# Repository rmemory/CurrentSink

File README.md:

Building a current sink for battery testing

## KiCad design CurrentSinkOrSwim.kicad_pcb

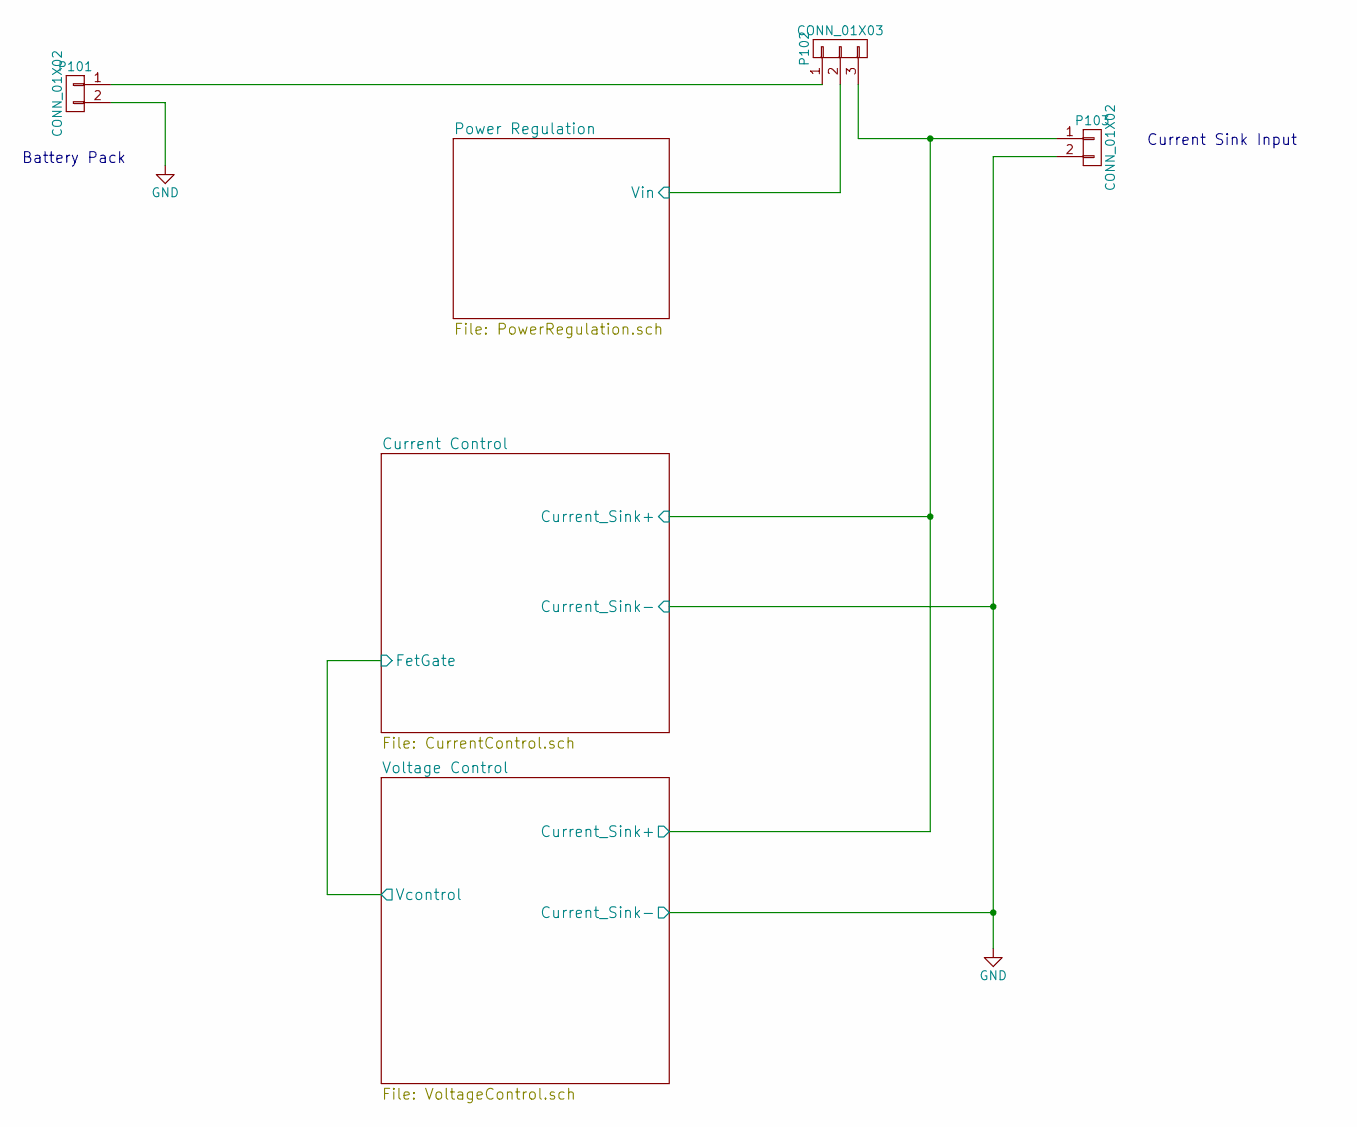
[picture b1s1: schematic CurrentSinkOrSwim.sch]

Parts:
P101, P103: CONN_01X02; Terminal_Block_200_mil; MPN OSTTC022162
P102: CONN_01X03; Pin_Header_Straight_1x03

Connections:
/Current Control/Current_Sink+: P102.3, P103.1; also elsewhere on the board
/Power Regulation/Vin: P102.2; also elsewhere on the board
GND: P101.2, P103.2; also elsewhere on the board
unnamed: P101.1, P102.1

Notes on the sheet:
Battery Pack
Current Sink Input

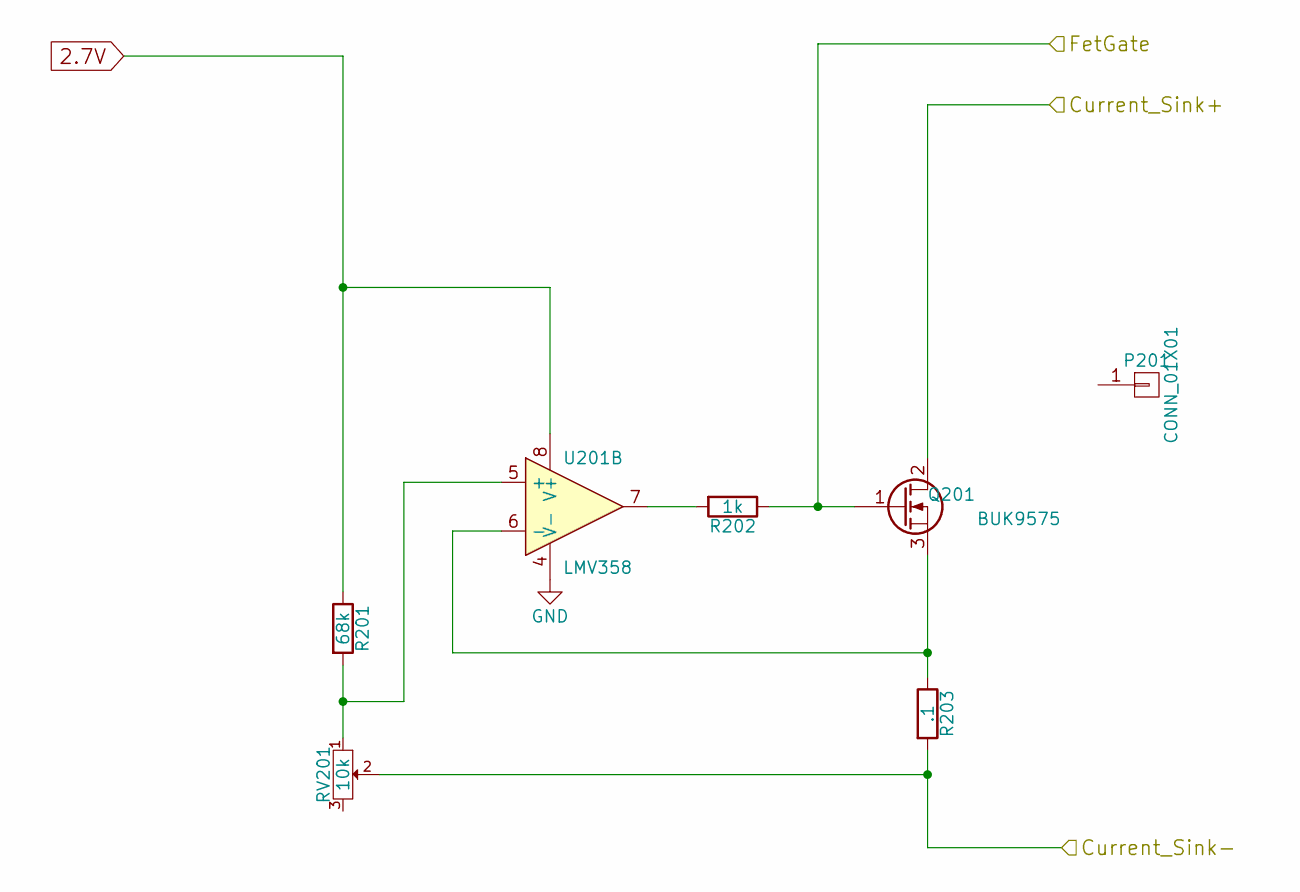
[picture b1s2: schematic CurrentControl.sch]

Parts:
P201: CONN_01X01; FA-T220-38E-ND; MPN FA-T220-38E-ND
Q201: BUK9575; TO-220_Neutral123_Vertical; MPN BUK9575-100A,127
R201: 68k; R_0805
R202: 1k; R_0805
R203: .1; Resistor_Horizontal_RM15mm; MPN AC01000001007JA100
RV201: 10k; P090L-02F25BR10K; MPN P090L-02F25BR10K
U201: LMV358; SOIC-8-N; MPN LMV358IDT

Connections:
2.7V: R201.1, U201.8 (V+); also elsewhere on the board
/Current Control/Current_Sink+: Q201.2 (D); also elsewhere on the board
/Current Control/FetGate: Q201.1 (G), R202.1; also elsewhere on the board
GND: R203.2, RV201.2, U201.4 (V-); also elsewhere on the board
unnamed: Q201.3 (S), R203.1, U201.6 (-)
unnamed: R201.2, RV201.1, U201.5 (+)
unnamed: R202.2, U201.7

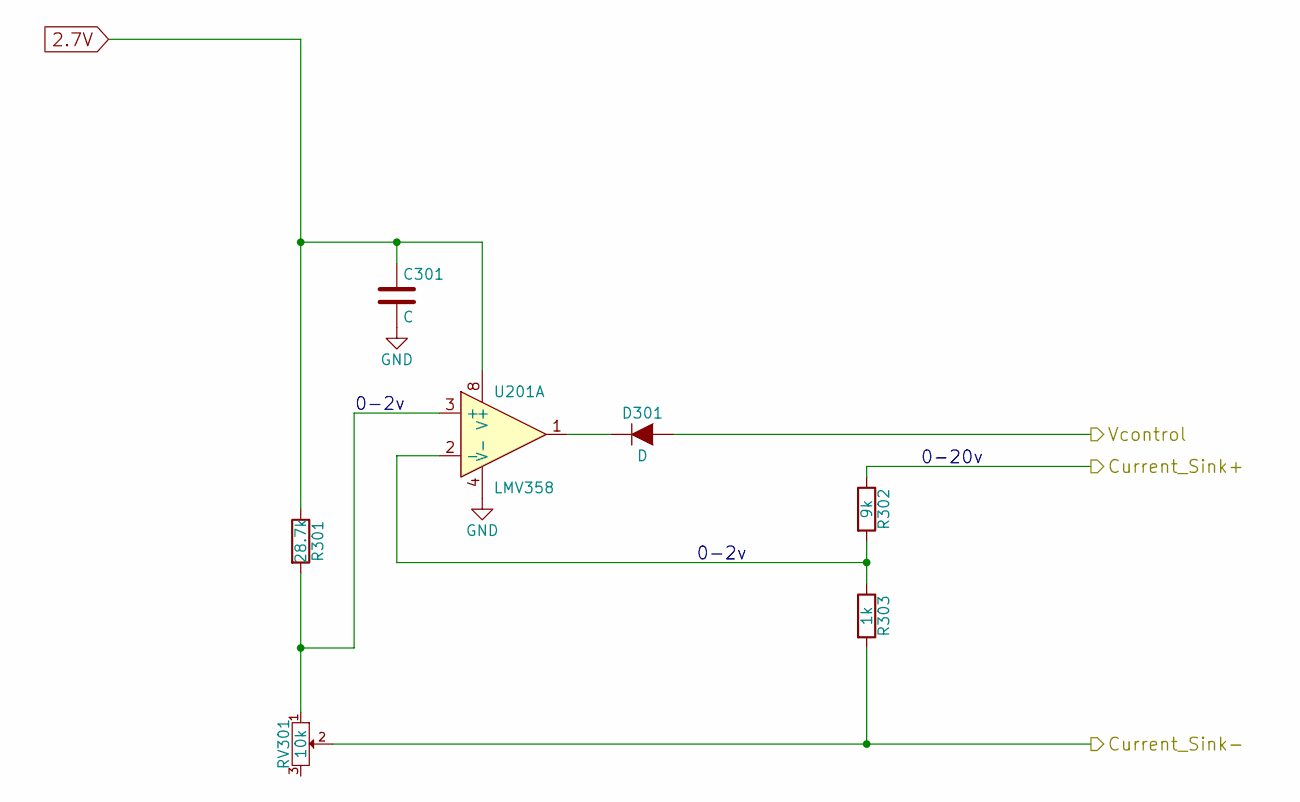
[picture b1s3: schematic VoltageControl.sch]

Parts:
C301: C; C_0805
D301: D; SMB-SMC_Universal_Handsoldering; MPN CD214B-R3600
R301: 28.7k; R_0805
R302: 9k; R_0805
R303: 1k; R_0805
RV301: 10k; P090L-02F25BR10K
U201: LMV358; SOIC-8-N; MPN LMV358IDT

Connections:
2.7V: C301.1, R301.1, U201.8 (V+); also elsewhere on the board
/Current Control/Current_Sink+: R302.1; also elsewhere on the board
/Current Control/FetGate: D301.2 (A); also elsewhere on the board
GND: C301.2, R303.2, RV301.2, U201.4 (V-); also elsewhere on the board
unnamed: D301.1 (K), U201.1
unnamed: R301.2, RV301.1, U201.3 (+)
unnamed: R302.2, R303.1, U201.2 (-)

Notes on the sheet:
0-2v
0-20v

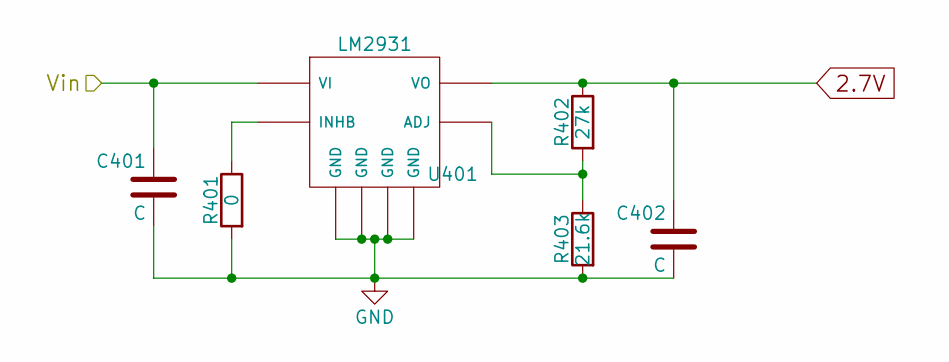
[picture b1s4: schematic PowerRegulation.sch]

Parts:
C401, C402: C; C_0805
R401: 0; R_0805
R402: 27k; R_0805
R403: 21.6k; R_0805
U401: LM2931; SOIC-8-N; MPN LM2931D-R

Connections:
2.7V: C402.1, R402.1, U401.1 (VO); also elsewhere on the board
/Power Regulation/Vin: C401.1, U401.8 (VI); also elsewhere on the board
GND: C401.2, C402.2, R401.2, R403.2, U401.2 (GND), U401.3 (GND), U401.6 (GND), U401.7 (GND); also elsewhere on the board
unnamed: R401.1, U401.5 (INHB)
unnamed: R402.2, R403.1, U401.4 (ADJ)

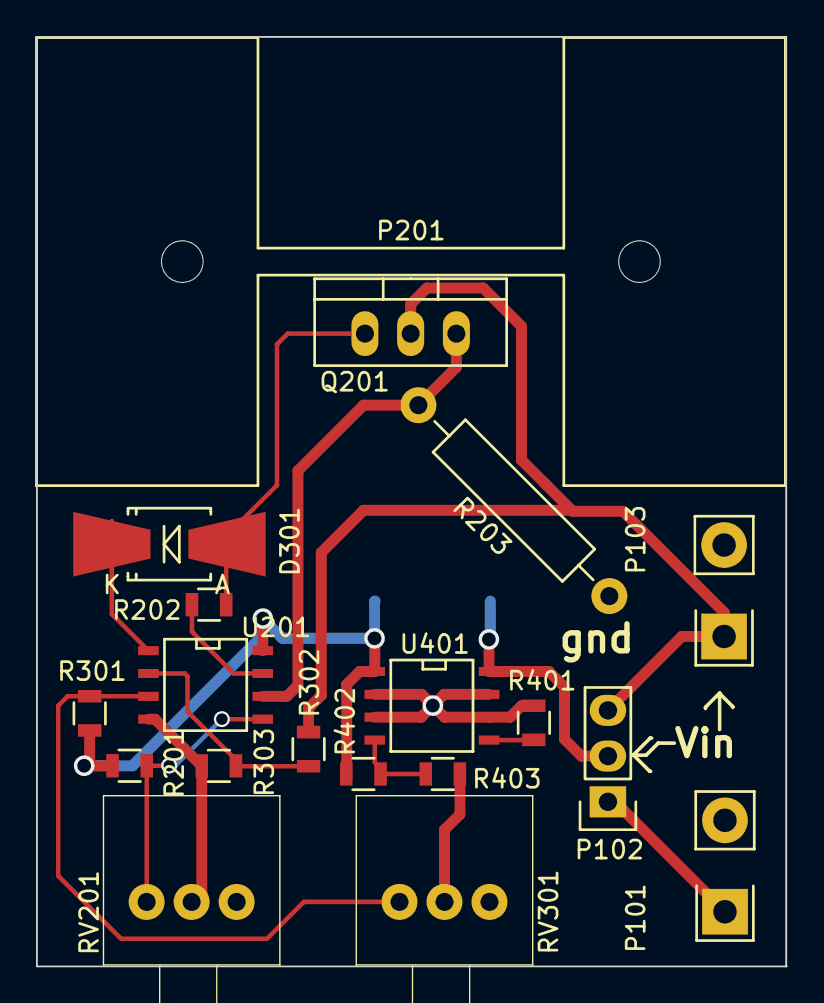
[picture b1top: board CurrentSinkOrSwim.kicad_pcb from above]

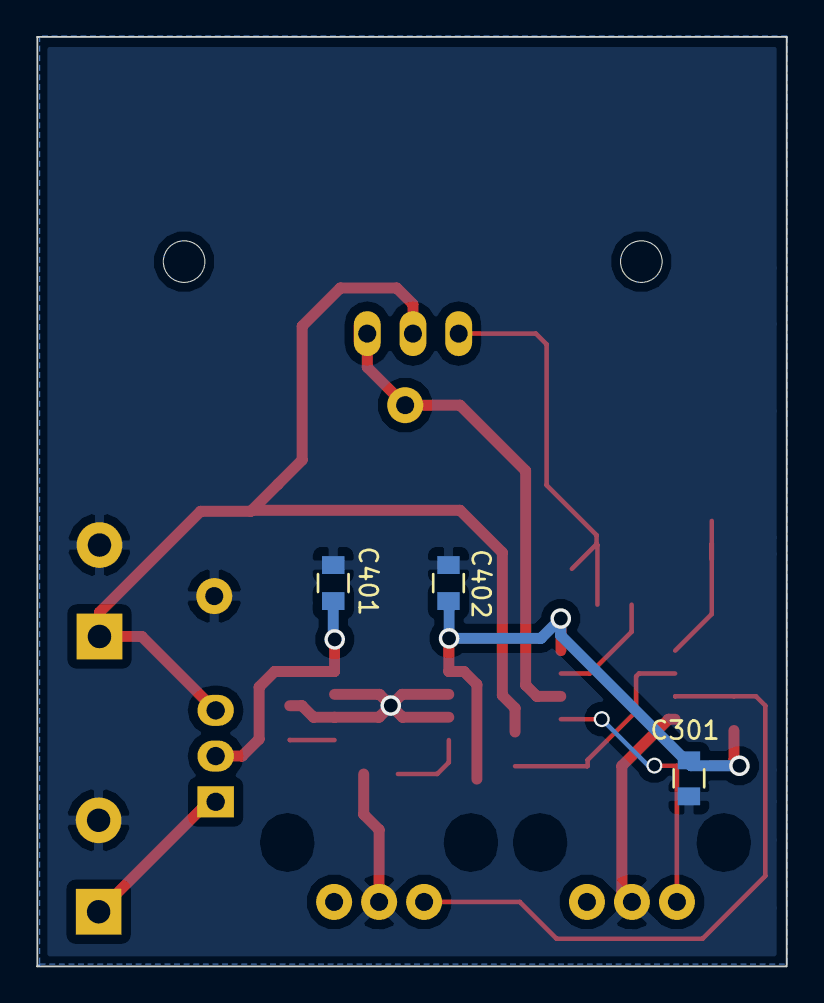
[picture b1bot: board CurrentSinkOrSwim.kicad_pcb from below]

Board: 2 copper layers, 41.7 x 51.6 mm, 22 parts (3 on the bottom side), 14 nets.

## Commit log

2016-08-17 Add README.md
2016-08-17 KiCad project and schematic creation
2016-08-27 Inital schmatic
2016-08-27 Remove backup file
2016-08-31 Add spice simulation, and also a couple part numbers for resister and FET
2016-09-07 minor mods to the schematic
2016-09-11 Added variable regulator to circuit
2016-09-14 updated spice simulation
2016-09-14 Added a cutoff voltage divider as well as cutoff op amp
2016-09-14 Updated spice model to use universal op amp
2016-09-16 Create hierarchical sheets
2016-09-16 Annotation completed
2016-09-16 Added a net list
2016-09-24 Add initial layout
2016-09-24 Add heat sink footprint
2016-09-26 Remove extra erroneus LMV358
2016-09-26 Forgot to update the layout after removing the extra LMV358
2016-09-26 First pass of all components on the top layer of the board
2016-09-26 Minor update to layout
2016-09-27 Add potentiometers
2016-09-27 Fixed divider resistors and found values
2016-09-27 Update layout based on new pot and reisistor values
2016-09-28 Reorganization of layout, shrink board size, add ground plane
2016-10-03 Lets try layout one more time. Starting layout from scratch
2016-10-06 Intermediate layout version 2
2016-10-06 A very compressed layout
2016-10-06 Minor adjustment to the pot position
2016-10-06 Found a missed 2.7 connection
2016-10-15 Another complete layout ... hopefully better.
2016-10-16 Minor update to the 2.7v track trying to improve path to ground for middle via
2016-10-18 Version 3 of the layout
2016-10-23 Add gerber files
2016-10-23 Gerber file updates
2016-10-23 Create zip file which has been submitted to oshpark
2016-10-24 Add preliminary BOM
2016-10-24 Final schematic and BOM and layout
